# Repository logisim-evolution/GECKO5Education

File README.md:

# GECKO5Education

The Gecko5Education is a new take on an open hardware educational platform. The ideas
of the Gecko5Education are based on the open hardware [ULX3S](https://github.com/emard/ulx3s) board,
the [Gecko4Education](https://gecko-wiki.ti.bfh.ch/) line of boards, and the recently developed 
[Leguan development board](https://leguan.ti.bfh.ch/).

3D preview:

This is a small (60.6x100 mm) standalone FPGA board 
for education, research and general purpose. It's open source and 
open hardware. It continues my line of educational boards used in the
past for teaching and research projects.

# Developer's guide
Information on how to use the board can be found [here](https://gecko5education.ti.bfh.ch)

# Production
The prototypes for these boards were produced and mounted by [Eurocircuits](https://www.eurocircuits.com/).

# Financement
The prototypes for these board (V1.0 and V1.1) were financed by the [computer architecture lab](https://www.epfl.ch/labs/lap/) of [EPFL](https://www.epfl.ch). Version V1.2 and the CPU-addon was financed by the [HuCE-microlab](https://www.bfh.ch/ti/en/research/research-areas/microlab/) of [BFH](https://www.bfh.ch).

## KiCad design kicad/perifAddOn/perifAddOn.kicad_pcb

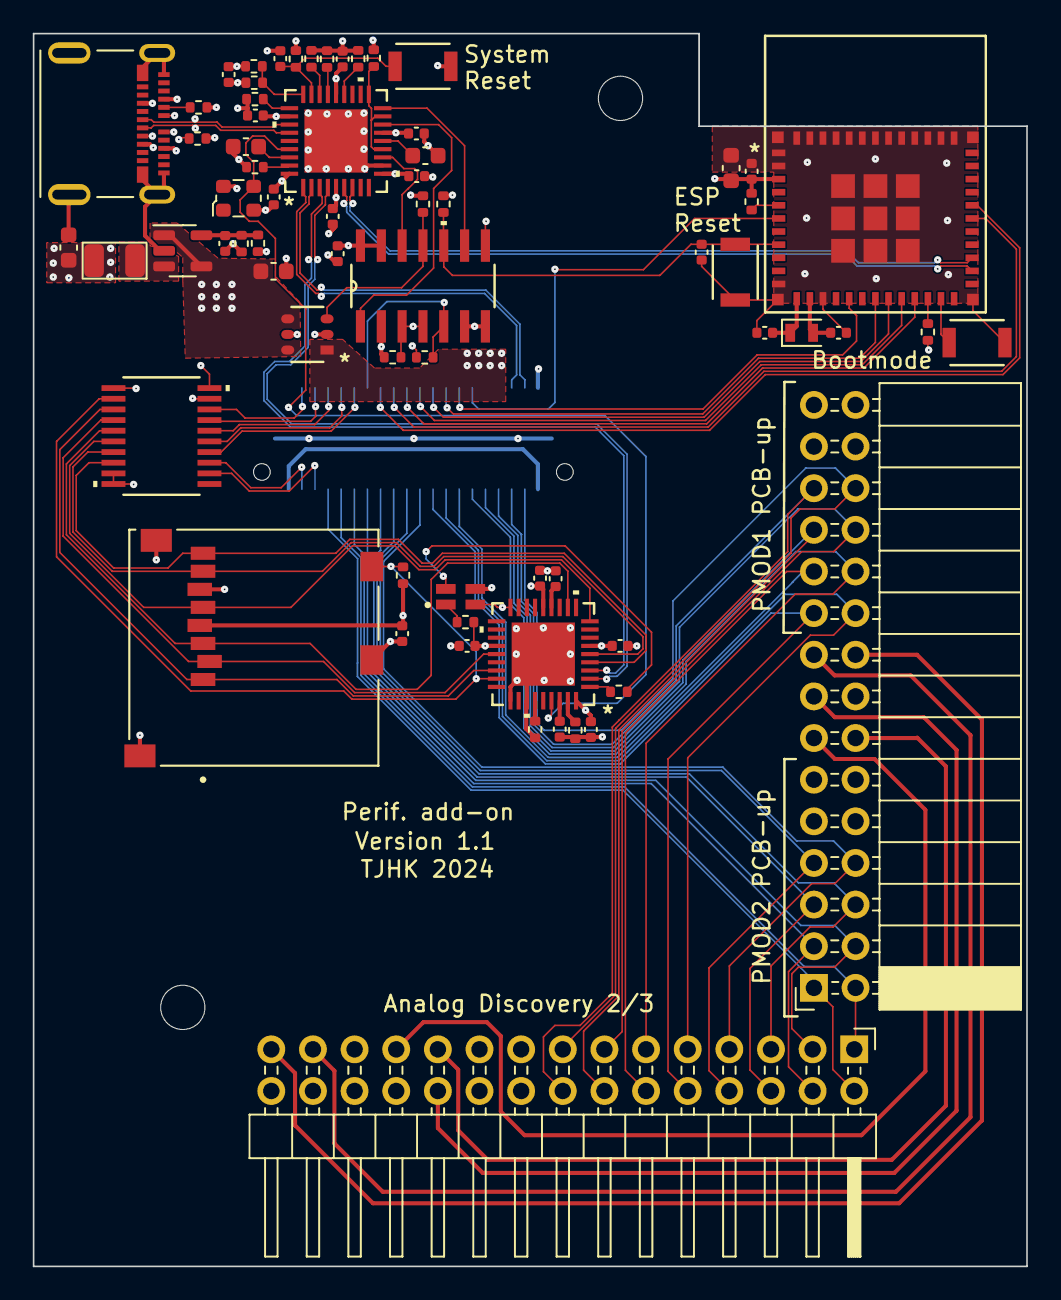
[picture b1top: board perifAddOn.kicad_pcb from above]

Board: 4 copper layers, 60.6 x 75.2 mm, 69 parts (1 on the bottom side), 90 nets.

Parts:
C1, C2, C4, C5, C6, C7, C8, C13, C14, C15, C19, C20, C22, C23, C24, C26: 100n; C_0402_1005Metric
C3, C9, C11, C12, C18: C1608X5R0J106M080AB; C_0603_1608Metric
C10: 18p; C_0402_1005Metric
C16, C17: 9pF; C_0402_1005Metric
C21, C25: 1uF; C_0402_1005Metric
D1: APHBM2012SURKCGKC; LED_APHBM2012SURKCGKC
J1: QTE-020-01-X-D-A; SAMTEC_QTE-020-01-X-D-A
J2: 105450-0101; MOLEX_105450-0101
J3: GTFP08431BEU; AMPHENOL_GTFP08431BEU
J4: Conn_02x15_Odd_Even; PinHeader_2x15_P2.54mm_Horizontal
J5: Conn_02x15_Odd_Even; PinSocket_2x15_P2.54mm_Horizontal
L1: LQM2HPN2R2MJ0L
R1, R2: 5k1; R_0402_1005Metric
R3, R4, R5, R6, R9, R10, R11, R12, R17, R18, R19, R20, R21, R24: 10k; R_0402_1005Metric
R7: 680k; R_0402_1005Metric
R8: 150k; R_0402_1005Metric
R13: 12k; R_0402_1005Metric
R14, R15, R16: 100k; R_0402_1005Metric
R22: 768R; R_0402_1005Metric
R23: 330R; R_0402_1005Metric
SW1, SW2, SW3: B3U-1000P[]; SW_B3U-1000P_OMR
U1: AP2281-3WG-7; SOT26_DIO
U2: SN74HC266DR; D14
U3: USB2513B-AEZC; QFN36_6X6MC_MCH
U4: NCP1529A; SOT-23-5
U5: ESP32-C3-MINI-1-N4; ESP32-C3-MINI-1_EXP
U6: USB2244-AEZG-06; QFN36_6X6MC_MCH
U7: TC7MBL3245CFTEL; TSSOP20_TOS
X1: ECS-2520MV-240-BL-TR; Oscillator_SMD_ECS_2520MV-xxx-xx-4Pin_2.5x2.0mm
Y1: RT2012-32.768-9-20-EXT-TR; Crystal_SMD_2012-2Pin_2.0x1.2mm

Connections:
+3.3V: C1.1, C2.1, C4.1, C5.1, C6.1, C7.1, C8.1, C10.1, C11.1, C15.2, C18.1, C20.2, C22.1, C23.1, C24.1, C26.1, J3.4 (VDD), J5.11, J5.12, J5.29, J5.30, L1.2, R3.2, R4.1, R5.1, R6.2, R7.1, R16.2, R17.2, R18.2, R19.2, R22.1, U2.2 (1B), U2.8 (3A), U2.13 (4B), U2.14 (VCC), U3.5 (VDDA33), U3.10 (VDDA33), U3.15 (VDD33), U3.23 (VDD33), U3.29 (VDDA33), U3.36 (VDD33), U5.3 (3V3), U6.6 (VDD33), U6.14 (VDD33), U6.22 (VDD33), U6.36 (VDDA33), U7.20, X1.4 (VDD)
+5V: C9.1, C13.1, J2.A4 (VBUS1), J2.A9 (VBUS2), J2.B4 (VBUS3), J2.B9 (VBUS4), R14.2, U1.4 (IN), U1.6 (IN), U4.1 (EN), U4.4 (VIN)
ADC_ChanA: J4.21, J5.14
ADC_ChanB: J4.22, J5.15
Clock24MHz: U3.33 (XTALIN/CLKIN), U6.33 (XTAL1(CLKIN)), X1.3 (OUT)
D1+: J2.A6 (D1+), J2.B6 (D2+), U3.31 (USBDP_UP)
D1-: J2.A7 (D1-), J2.B7 (D2-), U3.30 (USBDM_UP)
DAC_ChanA: J4.27, J5.17
DAC_ChanB: J4.29, J5.18
ESP32Drive: U2.9 (3B), U3.18 (PRTPWR3/BC_EN3)
EnFPGA: R4.2, U1.3 (EN), U2.11 (4Y)
EspD+: U3.7 (USBDP_DN3/PRT_DIS_P3), U5.27 (IO19)
EspD-: U3.6 (USBDM_DN3/PRT_DIS_M3), U5.26 (IO18)
EspEnable: C19.1, R5.2, SW2.1, U2.10 (3Y), U5.8 (EN)
EspIO3: J1.30, U5.6 (IO3)
EspIO4: J1.26, U5.18 (IO4)
EspIO5: J1.24, U5.19 (IO5)
EspIO6: J1.22, U5.20 (IO6)
EspIO7: J1.20, U5.21 (IO7)
EspIO10: J1.28, U5.16 (IO10)
EspRxd: J1.18, U5.30 (RXD0)
EspTxd: J1.16, U5.31 (TXD0)
FPGADrive: U2.12 (4A), U3.12 (PRTPWR1/BC_EN1)
GND: C1.2, C2.2, C3.2, C4.2, C5.2, C6.2, C7.2, C8.2, C9.2, C11.2, C12.2, C13.2, C14.2, C15.1, C16.2, C17.2, C18.2, C19.2, C20.1, C21.2, C22.2, C23.2, C24.2, C25.2, C26.2, D1.3, J1.40, J1.G1 (GND), J1.G2 (GND), J1.G3 (GND), J1.G4 (GND), J2.A1 (GND1), J2.A12 (GND2), J2.B1 (GND3), J2.B12 (GND4), J2.S1 (SHIELD), J2.S2 (SHIELD), J2.S3 (SHIELD), J2.S4 (SHIELD), J3.6 (VSS), J3.G1 (SHIELD_GND), J3.G2 (SHIELD_GND__1), J3.G3 (SHIELD_GND__2), J4.19, J4.20, J4.24, J4.25, J4.26, J4.28, J4.30, J5.9, J5.10, J5.16, J5.27, J5.28, R1.1, R2.1, R8.2, R9.1, R10.1, R11.1, R12.1, R13.1, R15.1, R20.2, R21.2, R24.2, SW1.2, SW2.2, SW3.2, U1.2 (GND), U1.5 (GND), U2.6 (2B), U2.7 (GND), U3.11 (TEST), U3.37 (EPAD), U4.2 (GND), U5.1 (GND), U5.2 (GND), U5.11 (GND), U5.14 (GND), U5.36 (GND), U5.37 (GND), U5.38 (GND), U5.39 (GND), U5.40 (GND), U5.41 (GND), U5.42 (GND), U5.43 (GND), U5.44 (GND), U5.45 (GND), U5.46 (GND), U5.47 (GND), U5.48 (GND), U5.49 (GND), U5.50 (GND), U5.51 (GND), U5.52 (GND), U5.53 (GND), U5.54 (GND), U5.55 (GND), U5.56 (GND), U5.57 (GND), U5.58 (GND), U5.59 (GND), U5.60 (GND), U5.61 (GND), U6.28 (TEST), U6.30 (SD_WP), U6.37 (EPAD), U7.1, U7.9, U7.10, X1.2 (GND)
unnamed: D1.1, R22.2
unnamed: D1.4, R23.2
unnamed: J1.01, J1.39
unnamed: J2.A5 (CC1), R1.2
unnamed: J2.B5 (CC2), R2.2
unnamed: J1.32, J1.34, U1.1 (OUT)
unnamed: C3.1, U3.14 (CRFILT)
unnamed: R10.2, U3.25 (HS_IND/CFG_SEL1)
unnamed: R6.1, U3.13 (OCS_N1), U3.17 (OCS_N2), U3.19 (OCS_N3)
unnamed: C12.1, U3.34 (PLLFILT)
unnamed: R13.2, U3.35 (RBIAS)
unnamed: C14.1, R16.1, SW1.1, U3.26 (RESET_N)
unnamed: R11.2, U3.24 (SCL/SMBCLK/CFG_SEL0)
unnamed: R12.2, U3.22 (SDA/SMBDATA/NON_REM1)
unnamed: R9.2, U3.28 (SUSP_IND/LOCAL_PWR/NON_REM0)
unnamed: R14.1, R15.2, U3.27 (VBUS_DET)
unnamed: C10.2, R7.2, R8.1, U4.5 (FB)
unnamed: L1.1, U4.3 (SW)
unnamed: C17.1, U5.12 (IO0), Y1.1
unnamed: C16.1, U5.13 (IO1), Y1.2
unnamed: R17.1, U5.5 (IO2)
unnamed: R18.1, U5.22 (IO8)
unnamed: SW3.1, U5.23 (IO9)
unnamed: R23.1, U6.1 (LED)
unnamed: R21.1, U6.35 (RBIAS)
unnamed: R20.1, U6.31 (TXD/SCK)
unnamed: C25.1, U6.13 (VDD18)
unnamed: C21.1, U6.34 (VDD18PLL)
PMOD1_1: J1.23, J4.10, J5.19
PMOD1_2: J1.27, J4.12, J5.21
PMOD1_3: J1.31, J4.14, J5.23
PMOD1_4: J1.35, J4.16, J5.25
PMOD1_7: J1.25, J4.9, J5.20
PMOD1_8: J1.29, J4.11, J5.22
PMOD1_9: J1.33, J4.13, J5.24
PMOD1_10: J1.37, J4.15, J5.26
PMOD2_1: J1.07, J4.2, J5.1
PMOD2_2: J1.11, J4.4, J5.3
PMOD2_3: J1.15, J4.6, J5.5
PMOD2_4: J1.19, J4.8, J5.7
PMOD2_7: J1.09, J4.1, J5.2
PMOD2_8: J1.13, J4.3, J5.4
PMOD2_9: J1.17, J4.5, J5.6
PMOD2_10: J1.21, J4.7, J5.8
SDCReset: J1.14, R24.1, U2.5 (2A)
SDCnReset: D1.2, R3.1, U2.3 (1Y), U2.4 (2Y), U6.18 (RESET_N), U7.19
SDCnResetDrive: U2.1 (1A), U3.16 (PRTPWR2/BC_EN2)
SdClk: J3.5 (CLK), U6.9 (SD_CLK), U7.6
SdClkB: J1.12, U7.14
SdCmd: J3.3 (CMD), U6.11 (SD_CMD), U7.5
SdCmdB: J1.10, U7.15
SdD0: J3.7 (DAT0), U6.5 (SD_D0), U7.7
SdD0B: J1.03, U7.13
SdD1: J3.8 (DAT1), U6.4 (SD_D1), U7.8
SdD1B: J1.05, U7.12
SdD2: J3.1 (DAT2), U6.25 (SD_D2), U7.3
SdD2B: J1.06, U7.17
SdD3: J3.2 (CD/DAT3), U6.23 (SD_D3), U7.4
SdD3B: J1.08, U7.16
SdcD+: U3.4 (USBDP_DN2/PRT_DIS_P2), U6.2 (USB+)
SdcD-: U3.3 (USBDM_DN2/PRT_DIS_M2), U6.3 (USB-)
SdnDet: J3.CD_PIN, R19.1, U6.26 (SD_NCD), U7.2
SdnDetB: J1.04, U7.18
UsbD+: J1.38, U3.2 (USBDP_DN1/PRT_DIS_P1)
UsbD-: J1.36, U3.1 (USBDM_DN1/PRT_DIS_M1)
VREF: J4.23, J5.13

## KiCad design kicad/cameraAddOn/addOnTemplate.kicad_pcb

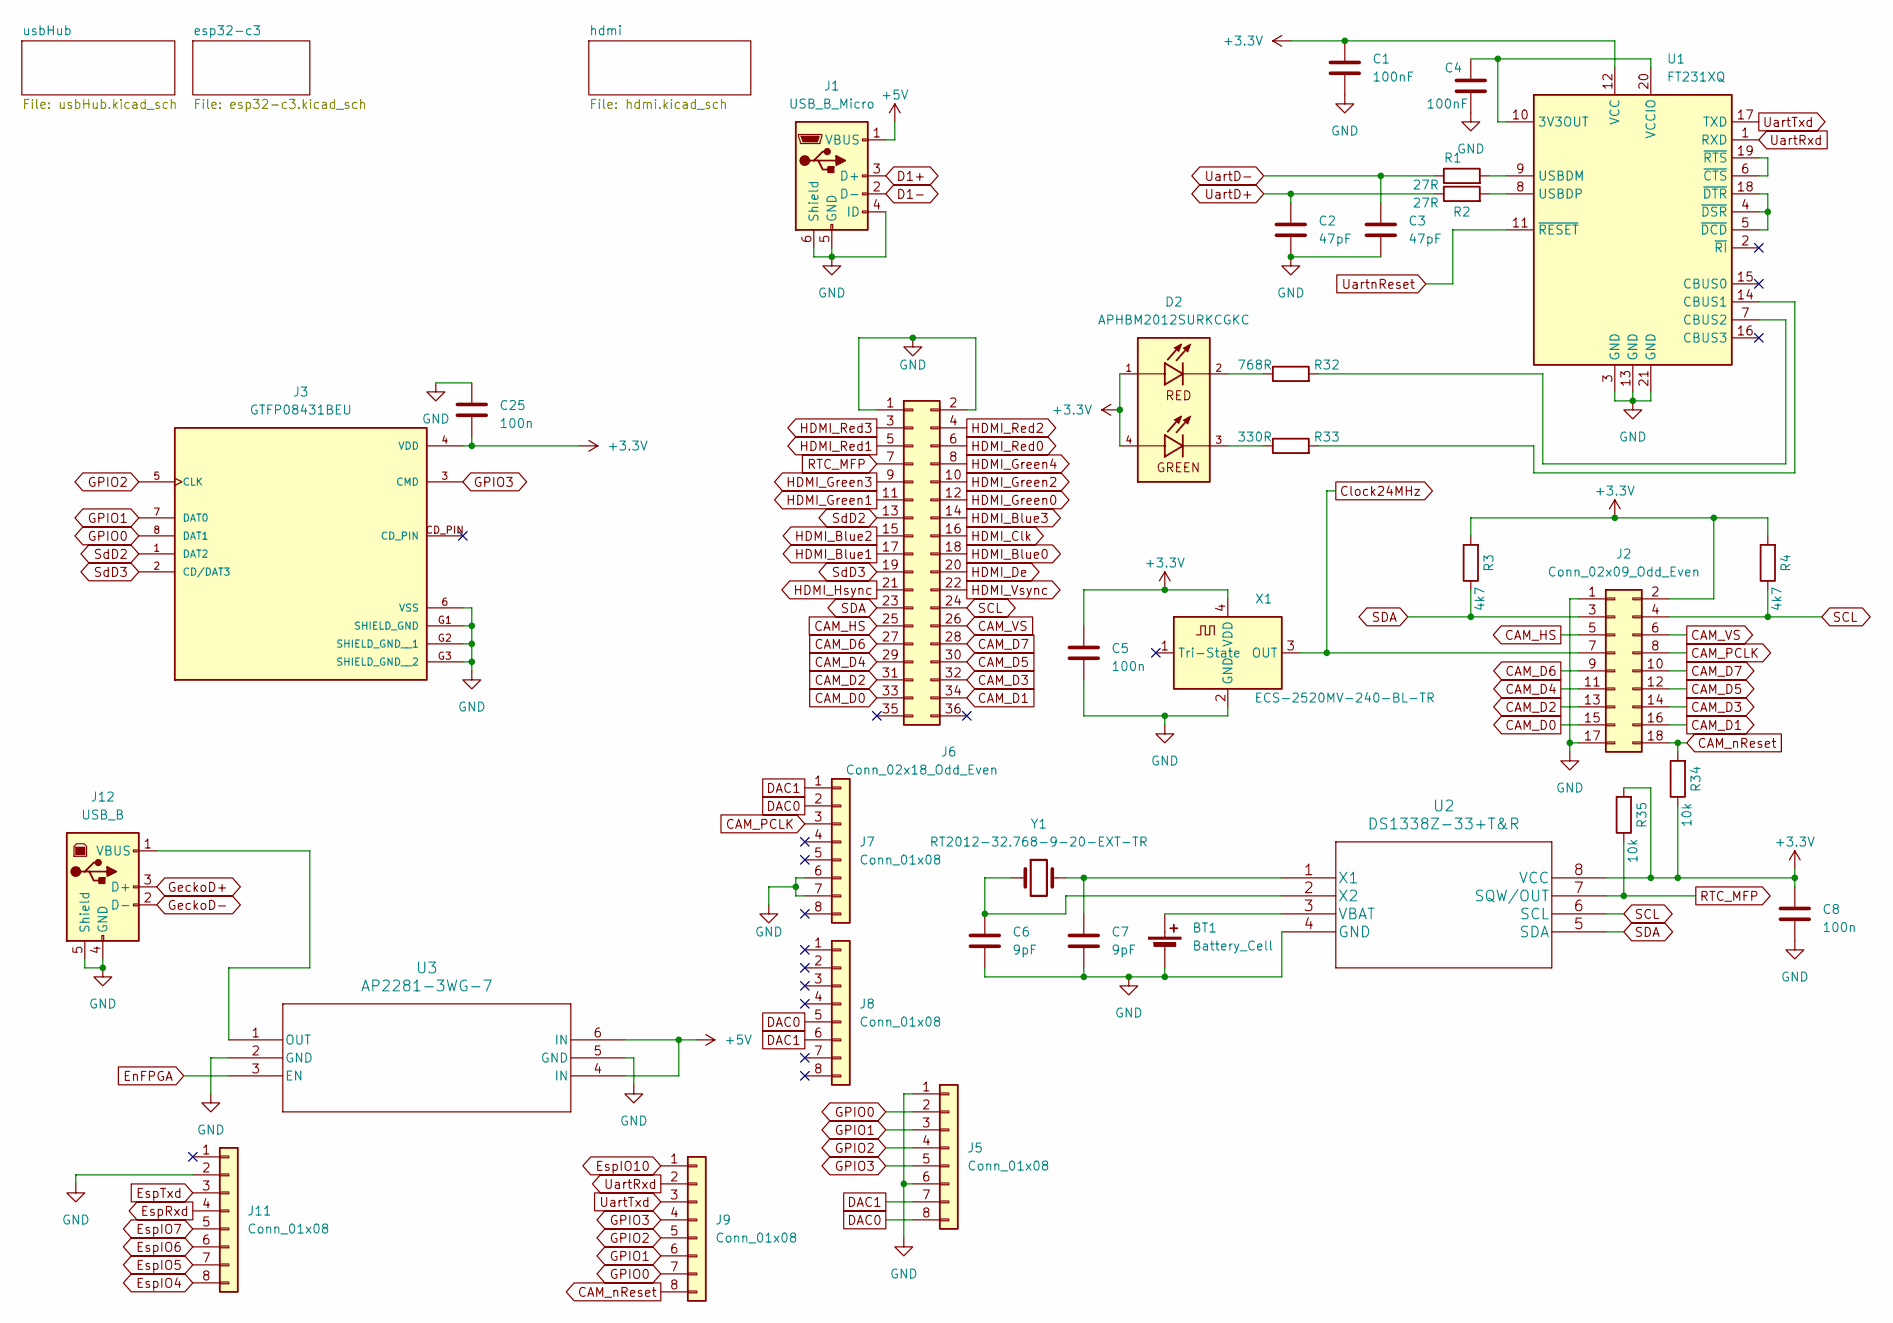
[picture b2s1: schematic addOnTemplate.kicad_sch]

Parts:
BT1: Battery_Cell; BatteryHolder_Keystone_1060_1x2032
C1, C4: 100nF; C_0402_1005Metric
C2, C3: 47pF; C_0402_1005Metric
C5, C8, C25: 100n; C_0402_1005Metric
C6, C7: 9pF; C_0402_1005Metric
D2: APHBM2012SURKCGKC; LED_APHBM2012SURKCGKC
J1: USB_B_Micro; USB_Micro-AB_Molex_47590-0001
J2: Conn_02x09_Odd_Even; PinSocket_2x09_P2.54mm_Horizontal
J3: GTFP08431BEU; AMPHENOL_GTFP08431BEU; PARTREV F
J5: Conn_01x08; PinHeader_2x04_P2.54mm_Horizontal
J6: Conn_02x18_Odd_Even; PinHeader_2x18_P2.54mm_Vertical
J7, J8, J9, J11: Conn_01x08; PinHeader_1x08_P2.54mm_Vertical
J12: USB_B; USB_A_Molex_67643_Horizontal
R1, R2: 27R; R_0402_1005Metric
R3, R4: 4k7; R_0402_1005Metric
R32: 768R; R_0402_1005Metric
R33: 330R; R_0402_1005Metric
R34, R35: 10k; R_0402_1005Metric
U1: FT231XQ; QFN-20-1EP_4x4mm_P0.5mm_EP2.5x2.5mm
U2: DS1338Z-33+T&R; DS1338Z-33&plus_T&R
U3: AP2281-3WG-7; SOT26_DIO
X1: ECS-2520MV-240-BL-TR; Oscillator_SMD_ECS_2520MV-xxx-xx-4Pin_2.5x2.0mm
Y1: RT2012-32.768-9-20-EXT-TR; Crystal_SMD_2012-2Pin_2.0x1.2mm

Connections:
+3.3V: C1.1, C5.1, C8.1, C25.2, D2.1, D2.4, J2.2, J3.4 (VDD), R3.2, R4.2, R34.1, R35.2, U1.12 (VCC), U2.8 (VCC), X1.4 (VDD); also elsewhere on the board
+5V: J1.1 (VBUS), U3.4 (IN), U3.6 (IN); also elsewhere on the board
CAM_D0: J2.15, J6.33
CAM_D1: J2.16, J6.34
CAM_D2: J2.13, J6.31
CAM_D3: J2.14, J6.32
CAM_D4: J2.11, J6.29
CAM_D5: J2.12, J6.30
CAM_D6: J2.9, J6.27
CAM_D7: J2.10, J6.28
CAM_HS: J2.5, J6.25
CAM_PCLK: J2.8, J7.3
CAM_VS: J2.6, J6.26
CAM_nReset: J2.18, J9.8, R34.2
Clock24MHz: J2.7, X1.3 (OUT); also elsewhere on the board
D1+: J1.3 (D+); also elsewhere on the board
D1-: J1.2 (D-); also elsewhere on the board
DAC0: J5.8, J7.2, J8.5
DAC1: J5.7, J7.1, J8.6
EnFPGA: U3.3 (EN); also elsewhere on the board
EspIO4: J11.8; also elsewhere on the board
EspIO5: J11.7; also elsewhere on the board
EspIO6: J11.6; also elsewhere on the board
EspIO7: J11.5; also elsewhere on the board
EspIO10: J9.1; also elsewhere on the board
EspRxd: J11.4; also elsewhere on the board
EspTxd: J11.3; also elsewhere on the board
GND: BT1.2 (-), C1.2, C2.2, C3.2, C4.2, C5.2, C6.2, C7.2, C8.2, C25.1, J1.4 (ID), J1.5 (GND), J1.6 (Shield), J2.1, J2.17, J3.6 (VSS), J3.G1 (SHIELD_GND), J3.G2 (SHIELD_GND__1), J3.G3 (SHIELD_GND__2), J5.1, J5.6, J6.1, J6.2, J7.6, J7.7, J11.2, J12.4 (GND), J12.5 (Shield), U1.3 (GND), U1.13 (GND), U1.21 (GND), U2.4 (GND), U3.2 (GND), U3.5 (GND), X1.2 (GND); also elsewhere on the board
GPIO0: J3.8 (DAT1), J5.2, J9.7
GPIO1: J3.7 (DAT0), J5.3, J9.6
GPIO2: J3.5 (CLK), J5.4, J9.5
GPIO3: J3.3 (CMD), J5.5, J9.4
GeckoD+: J12.3 (D+); also elsewhere on the board
GeckoD-: J12.2 (D-); also elsewhere on the board
HDMI_Blue0: J6.18; also elsewhere on the board
HDMI_Blue1: J6.17; also elsewhere on the board
HDMI_Blue2: J6.15; also elsewhere on the board
HDMI_Blue3: J6.14; also elsewhere on the board
HDMI_Clk: J6.16; also elsewhere on the board
HDMI_De: J6.20; also elsewhere on the board
HDMI_Green0: J6.12; also elsewhere on the board
HDMI_Green1: J6.11; also elsewhere on the board
HDMI_Green2: J6.10; also elsewhere on the board
HDMI_Green3: J6.9; also elsewhere on the board
HDMI_Green4: J6.8; also elsewhere on the board
HDMI_Hsync: J6.21; also elsewhere on the board
HDMI_Red0: J6.6; also elsewhere on the board
HDMI_Red1: J6.5; also elsewhere on the board
HDMI_Red2: J6.4; also elsewhere on the board
HDMI_Red3: J6.3; also elsewhere on the board
HDMI_Vsync: J6.22; also elsewhere on the board
unnamed: BT1.1 (+), U2.3 (VBAT)
unnamed: D2.2, R32.1
unnamed: D2.3, R33.1
unnamed: J12.1 (VBUS), U3.1 (OUT)
unnamed: C4.1, U1.10 (3V3OUT), U1.20 (VCCIO)
unnamed: R33.2, U1.14 (CBUS1)
unnamed: R32.2, U1.7 (CBUS2)
unnamed: R1.2, U1.9 (USBDM)
unnamed: R2.2, U1.8 (USBDP)
unnamed: U1.6 (~CTS), U1.19 (~RTS)
unnamed: U1.4 (~DSR), U1.5 (~DCD), U1.18 (~DTR)
unnamed: C7.1, U2.1 (X1), Y1.2
unnamed: C6.1, U2.2 (X2), Y1.1
RTC_MFP: J6.7, R35.1, U2.7 (SQW/OUT)
SCL: J2.4, J6.24, R4.1, U2.6 (SCL)
SDA: J2.3, J6.23, R3.1, U2.5 (SDA)
SdD2: J3.1 (DAT2), J6.13
SdD3: J3.2 (CD/DAT3), J6.19
UartD+: C2.1, R2.1; also elsewhere on the board
UartD-: C3.1, R1.1; also elsewhere on the board
UartRxd: J9.2, U1.1 (RXD)
UartTxd: J9.3, U1.17 (TXD)
UartnReset: U1.11 (~RESET); also elsewhere on the board

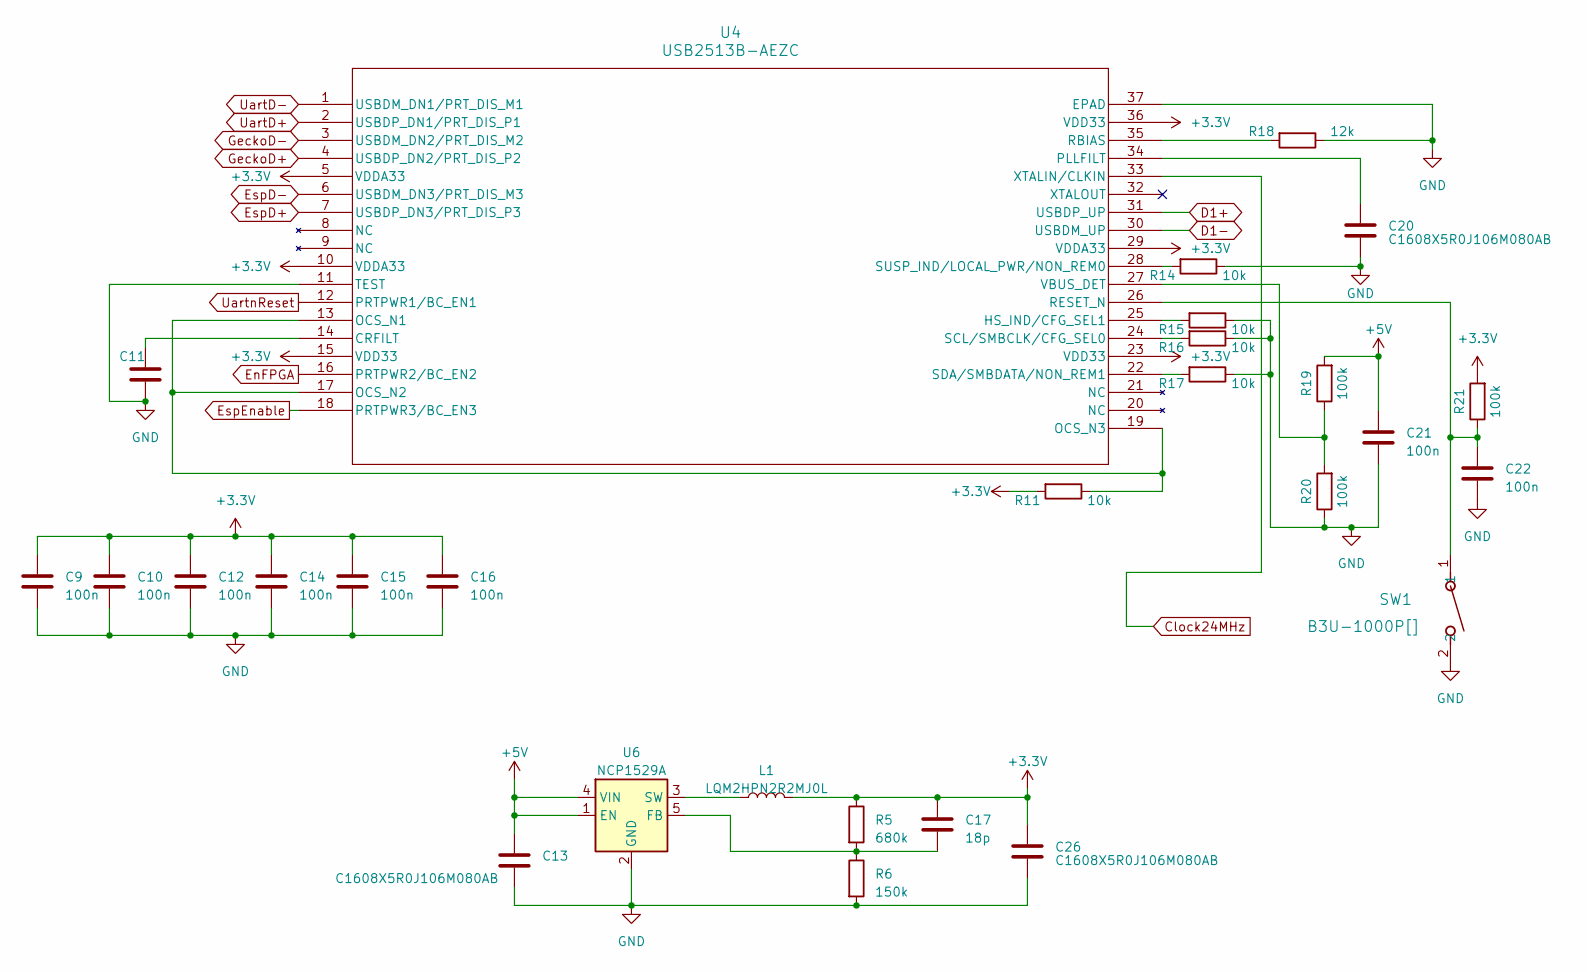
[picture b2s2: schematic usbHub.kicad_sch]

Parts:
C9, C10, C12, C14, C15, C16, C21, C22: 100n; C_0402_1005Metric
C11, C13, C20, C26: C1608X5R0J106M080AB; C_0603_1608Metric
C17: 18p; C_0402_1005Metric
L1: LQM2HPN2R2MJ0L
R5: 680k; R_0402_1005Metric
R6: 150k; R_0402_1005Metric
R11, R14, R15, R16, R17: 10k; R_0402_1005Metric
R18: 12k; R_0402_1005Metric
R19, R20, R21: 100k; R_0402_1005Metric
SW1: B3U-1000P[]; SW_B3U-1000P_OMR
U4: USB2513B-AEZC; QFN36_6X6MC_MCH
U6: NCP1529A; SOT-23-5

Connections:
+3.3V: C9.1, C10.1, C12.1, C14.1, C15.1, C16.1, C17.1, C26.1, L1.2, R5.1, R11.2, R21.2, U4.5 (VDDA33), U4.10 (VDDA33), U4.15 (VDD33), U4.23 (VDD33), U4.29 (VDDA33), U4.36 (VDD33); also elsewhere on the board
+5V: C13.1, C21.1, R19.2, U6.1 (EN), U6.4 (VIN); also elsewhere on the board
Clock24MHz: U4.33 (XTALIN/CLKIN); also elsewhere on the board
D1+: U4.31 (USBDP_UP); also elsewhere on the board
D1-: U4.30 (USBDM_UP); also elsewhere on the board
EnFPGA: U4.16 (PRTPWR2/BC_EN2); also elsewhere on the board
EspD+: U4.7 (USBDP_DN3/PRT_DIS_P3); also elsewhere on the board
EspD-: U4.6 (USBDM_DN3/PRT_DIS_M3); also elsewhere on the board
EspEnable: U4.18 (PRTPWR3/BC_EN3); also elsewhere on the board
GND: C9.2, C10.2, C11.2, C12.2, C13.2, C14.2, C15.2, C16.2, C20.2, C21.2, C22.2, C26.2, R6.2, R14.1, R15.1, R16.1, R17.1, R18.1, R20.1, SW1.2, U4.11 (TEST), U4.37 (EPAD), U6.2 (GND); also elsewhere on the board
GeckoD+: U4.4 (USBDP_DN2/PRT_DIS_P2); also elsewhere on the board
GeckoD-: U4.3 (USBDM_DN2/PRT_DIS_M2); also elsewhere on the board
unnamed: C11.1, U4.14 (CRFILT)
unnamed: R15.2, U4.25 (HS_IND/CFG_SEL1)
unnamed: R11.1, U4.13 (OCS_N1), U4.17 (OCS_N2), U4.19 (OCS_N3)
unnamed: C20.1, U4.34 (PLLFILT)
unnamed: R18.2, U4.35 (RBIAS)
unnamed: C22.1, R21.1, SW1.1, U4.26 (RESET_N)
unnamed: R16.2, U4.24 (SCL/SMBCLK/CFG_SEL0)
unnamed: R17.2, U4.22 (SDA/SMBDATA/NON_REM1)
unnamed: R14.2, U4.28 (SUSP_IND/LOCAL_PWR/NON_REM0)
unnamed: R19.1, R20.2, U4.27 (VBUS_DET)
unnamed: C17.2, R5.2, R6.1, U6.5 (FB)
unnamed: L1.1, U6.3 (SW)
UartD+: U4.2 (USBDP_DN1/PRT_DIS_P1); also elsewhere on the board
UartD-: U4.1 (USBDM_DN1/PRT_DIS_M1); also elsewhere on the board
UartnReset: U4.12 (PRTPWR1/BC_EN1); also elsewhere on the board

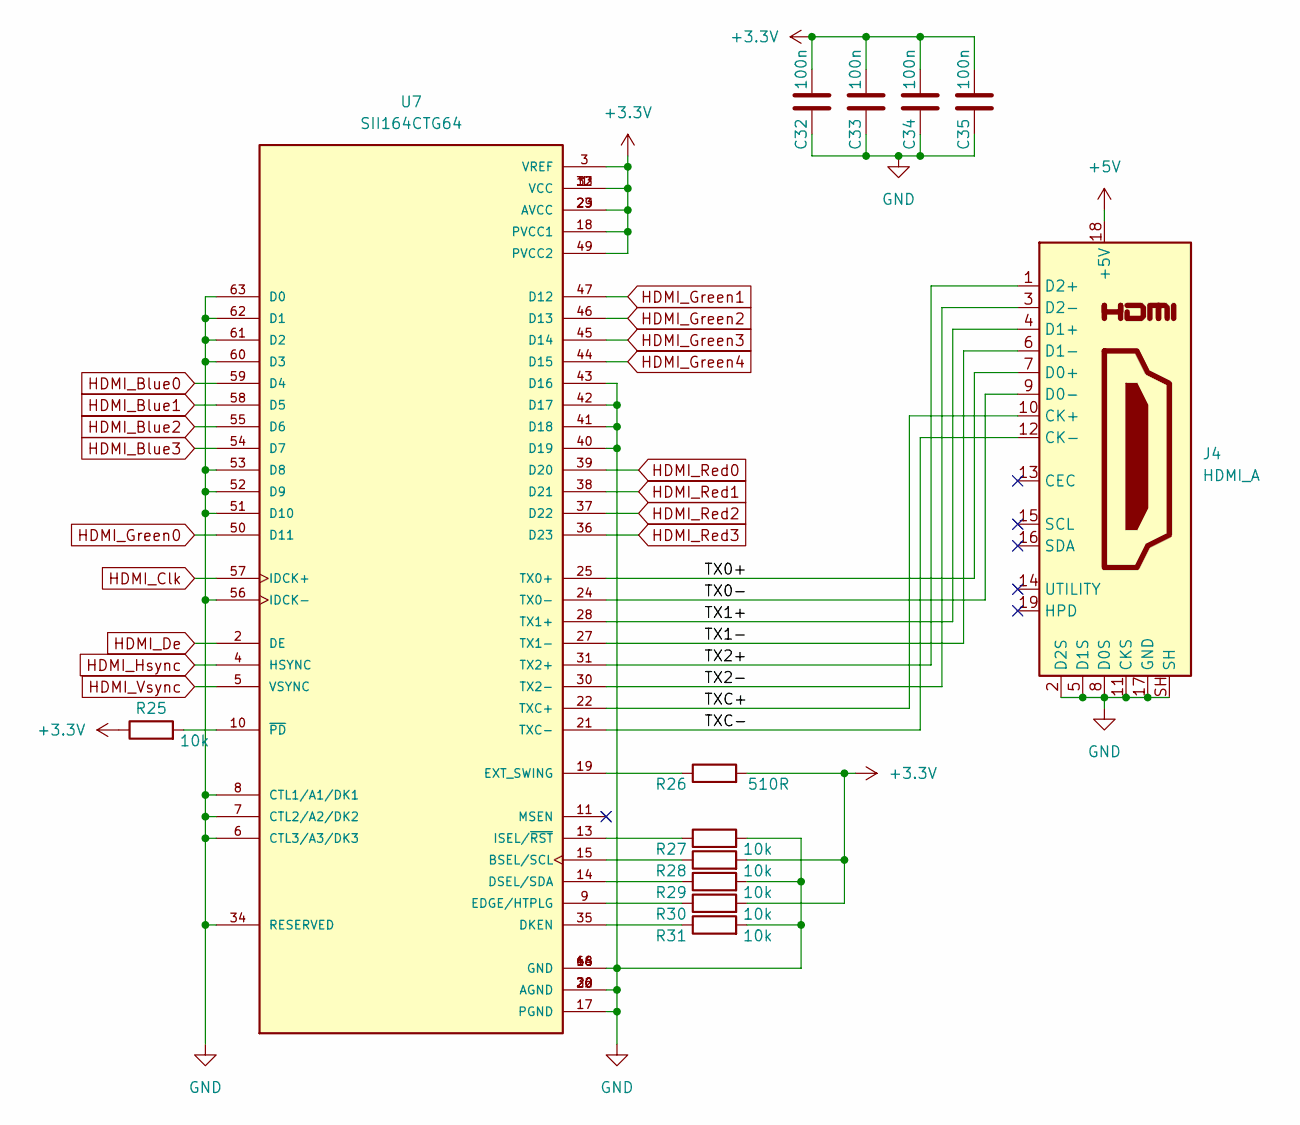
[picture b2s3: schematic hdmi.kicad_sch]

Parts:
C32, C33, C34, C35: 100n; R_0402_1005Metric
J4: HDMI_A; HDMI_A_Molex_208658-1001_Horizontal
R25, R27, R28, R29, R30, R31: 10k; R_0402_1005Metric
R26: 510R; R_0402_1005Metric
U7: SII164CTG64; QFP50P1200X1200X120-64N; PARTREV E; DigiKey_Part_Number 220-2189-ND

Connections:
+3.3V: C32.2, C33.2, C34.2, C35.2, R25.1, R26.2, R28.2, R30.2, U7.1 (VCC), U7.3 (VREF), U7.12 (VCC), U7.18 (PVCC1), U7.23 (AVCC), U7.29 (AVCC), U7.33 (VCC), U7.49 (PVCC2); also elsewhere on the board
+5V: J4.18 (+5V); also elsewhere on the board
/hdmi/TX0+: J4.7 (D0+), U7.25 (TX0+)
/hdmi/TX0-: J4.9 (D0-), U7.24 (TX0-)
/hdmi/TX1+: J4.4 (D1+), U7.28 (TX1+)
/hdmi/TX1-: J4.6 (D1-), U7.27 (TX1-)
/hdmi/TX2+: J4.1 (D2+), U7.31 (TX2+)
/hdmi/TX2-: J4.3 (D2-), U7.30 (TX2-)
/hdmi/TXC+: J4.10 (CK+), U7.22 (TXC+)
/hdmi/TXC-: J4.12 (CK-), U7.21 (TXC-)
GND: C32.1, C33.1, C34.1, C35.1, J4.2 (D2S), J4.5 (D1S), J4.8 (D0S), J4.11 (CKS), J4.17 (GND), J4.SH, R27.2, R29.2, R31.2, U7.6 (CTL3/A3/DK3), U7.7 (CTL2/A2/DK2), U7.8 (CTL1/A1/DK1), U7.16 (GND), U7.17 (PGND), U7.20 (AGND), U7.26 (AGND), U7.32 (AGND), U7.34 (RESERVED), U7.40 (D19), U7.41 (D18), U7.42 (D17), U7.43 (D16), U7.48 (GND), U7.51 (D10), U7.52 (D9), U7.53 (D8), U7.56 (IDCK-), U7.60 (D3), U7.61 (D2), U7.62 (D1), U7.63 (D0), U7.64 (GND); also elsewhere on the board
HDMI_Blue0: U7.59 (D4); also elsewhere on the board
HDMI_Blue1: U7.58 (D5); also elsewhere on the board
HDMI_Blue2: U7.55 (D6); also elsewhere on the board
HDMI_Blue3: U7.54 (D7); also elsewhere on the board
HDMI_Clk: U7.57 (IDCK+); also elsewhere on the board
HDMI_De: U7.2 (DE); also elsewhere on the board
HDMI_Green0: U7.50 (D11); also elsewhere on the board
HDMI_Green1: U7.47 (D12); also elsewhere on the board
HDMI_Green2: U7.46 (D13); also elsewhere on the board
HDMI_Green3: U7.45 (D14); also elsewhere on the board
HDMI_Green4: U7.44 (D15); also elsewhere on the board
HDMI_Hsync: U7.4 (HSYNC); also elsewhere on the board
HDMI_Red0: U7.39 (D20); also elsewhere on the board
HDMI_Red1: U7.38 (D21); also elsewhere on the board
HDMI_Red2: U7.37 (D22); also elsewhere on the board
HDMI_Red3: U7.36 (D23); also elsewhere on the board
HDMI_Vsync: U7.5 (VSYNC); also elsewhere on the board
unnamed: R28.1, U7.15 (BSEL/SCL)
unnamed: R31.1, U7.35 (DKEN)
unnamed: R29.1, U7.14 (DSEL/SDA)
unnamed: R30.1, U7.9 (EDGE/HTPLG)
unnamed: R26.1, U7.19 (EXT_SWING)
unnamed: R27.1, U7.13 (ISEL/~RST)
unnamed: R25.2, U7.10 (~PD)

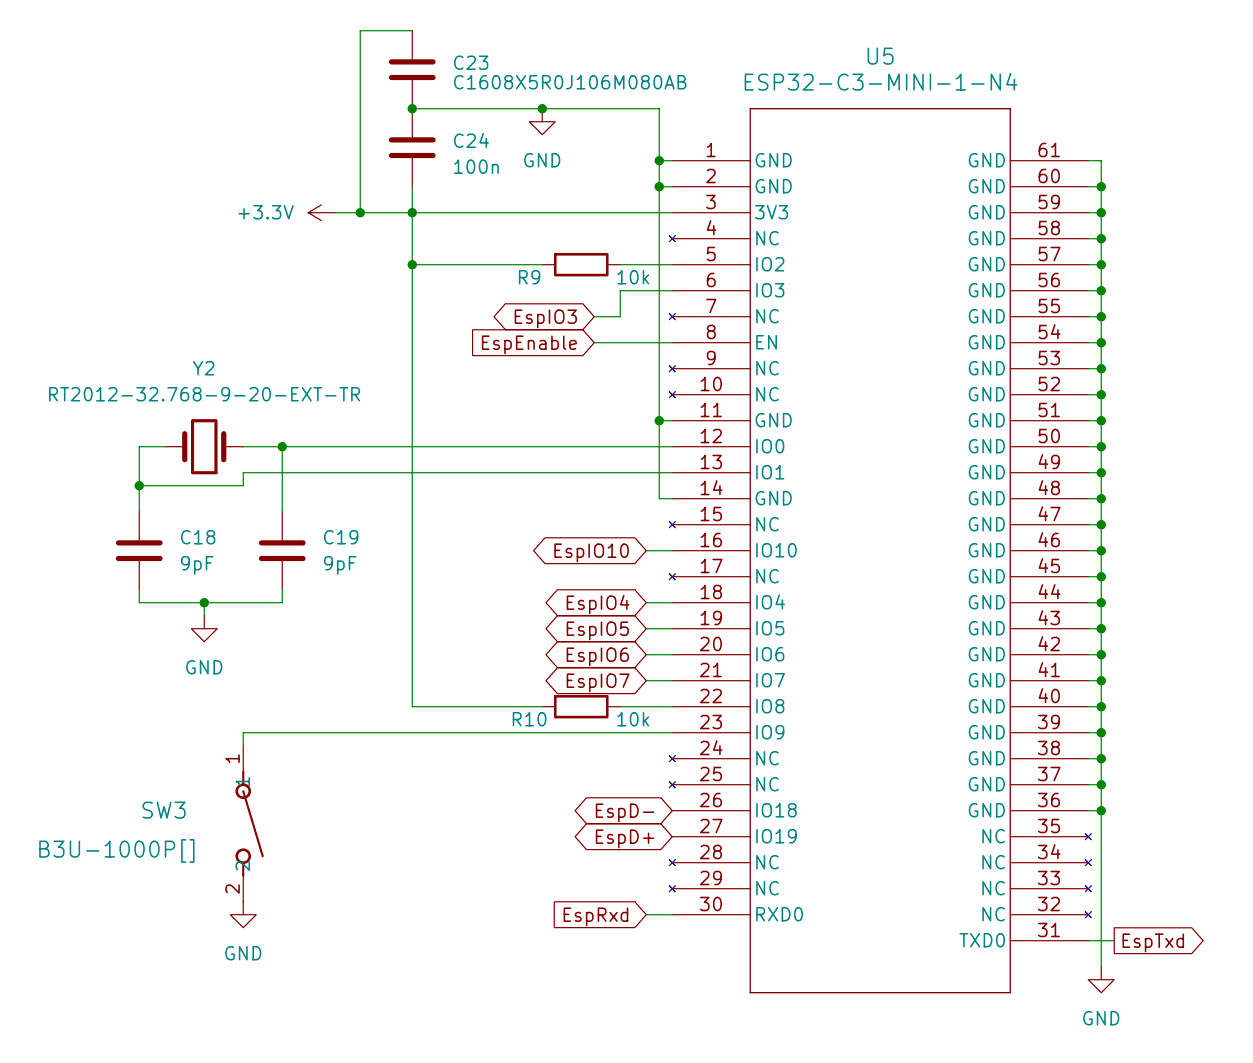
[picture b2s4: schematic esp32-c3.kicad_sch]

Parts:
C18, C19: 9pF; C_0402_1005Metric
C23: C1608X5R0J106M080AB; C_0603_1608Metric
C24: 100n; C_0402_1005Metric
R9, R10: 10k; R_0402_1005Metric
SW3: B3U-1000P[]; SW_B3U-1000P_OMR
U5: ESP32-C3-MINI-1-N4; ESP32-C3-MINI-1_EXP
Y2: RT2012-32.768-9-20-EXT-TR; Crystal_SMD_2012-2Pin_2.0x1.2mm

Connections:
+3.3V: C23.1, C24.2, R9.2, R10.2, U5.3 (3V3); also elsewhere on the board
EspD+: U5.27 (IO19); also elsewhere on the board
EspD-: U5.26 (IO18); also elsewhere on the board
EspEnable: U5.8 (EN); also elsewhere on the board
EspIO3: U5.6 (IO3)
EspIO4: U5.18 (IO4); also elsewhere on the board
EspIO5: U5.19 (IO5); also elsewhere on the board
EspIO6: U5.20 (IO6); also elsewhere on the board
EspIO7: U5.21 (IO7); also elsewhere on the board
EspIO10: U5.16 (IO10); also elsewhere on the board
EspRxd: U5.30 (RXD0); also elsewhere on the board
EspTxd: U5.31 (TXD0); also elsewhere on the board
GND: C18.2, C19.2, C23.2, C24.1, SW3.2, U5.1 (GND), U5.2 (GND), U5.11 (GND), U5.14 (GND), U5.36 (GND), U5.37 (GND), U5.38 (GND), U5.39 (GND), U5.40 (GND), U5.41 (GND), U5.42 (GND), U5.43 (GND), U5.44 (GND), U5.45 (GND), U5.46 (GND), U5.47 (GND), U5.48 (GND), U5.49 (GND), U5.50 (GND), U5.51 (GND), U5.52 (GND), U5.53 (GND), U5.54 (GND), U5.55 (GND), U5.56 (GND), U5.57 (GND), U5.58 (GND), U5.59 (GND), U5.60 (GND), U5.61 (GND); also elsewhere on the board
unnamed: C19.1, U5.12 (IO0), Y2.1
unnamed: C18.1, U5.13 (IO1), Y2.2
unnamed: R9.1, U5.5 (IO2)
unnamed: R10.1, U5.22 (IO8)
unnamed: SW3.1, U5.23 (IO9)

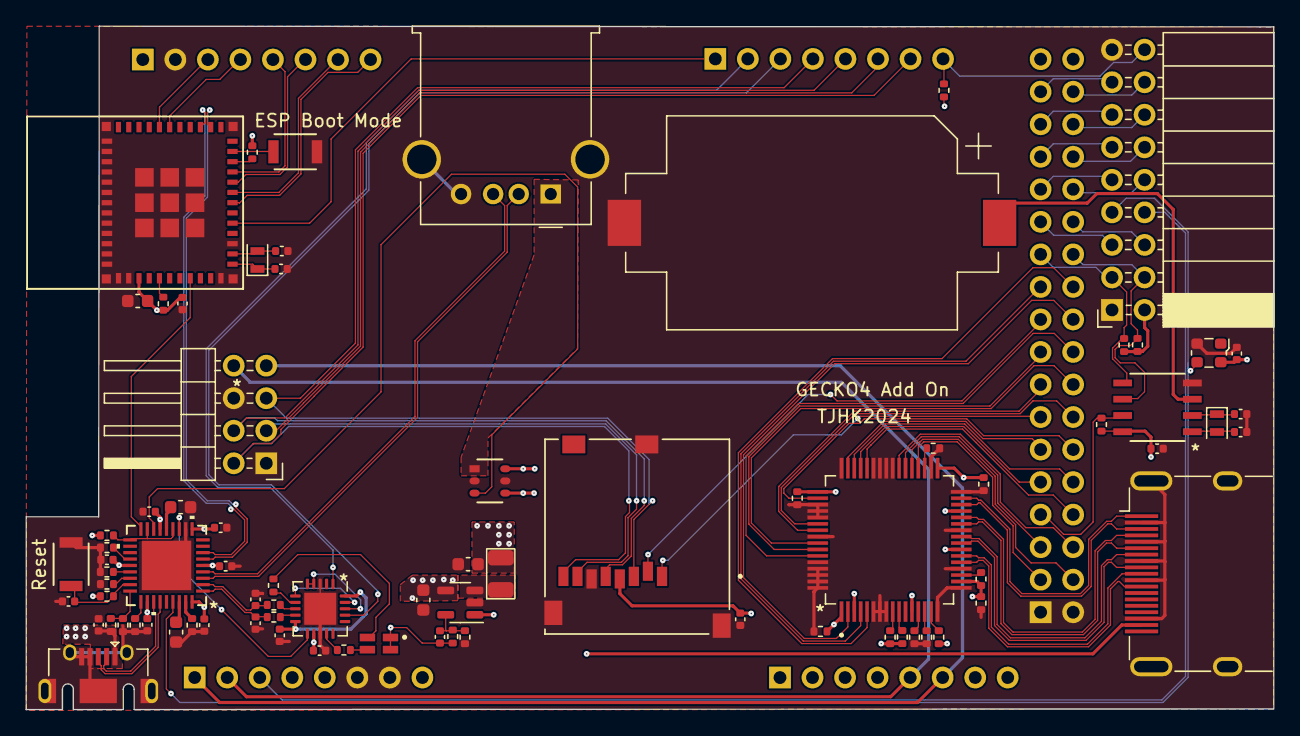
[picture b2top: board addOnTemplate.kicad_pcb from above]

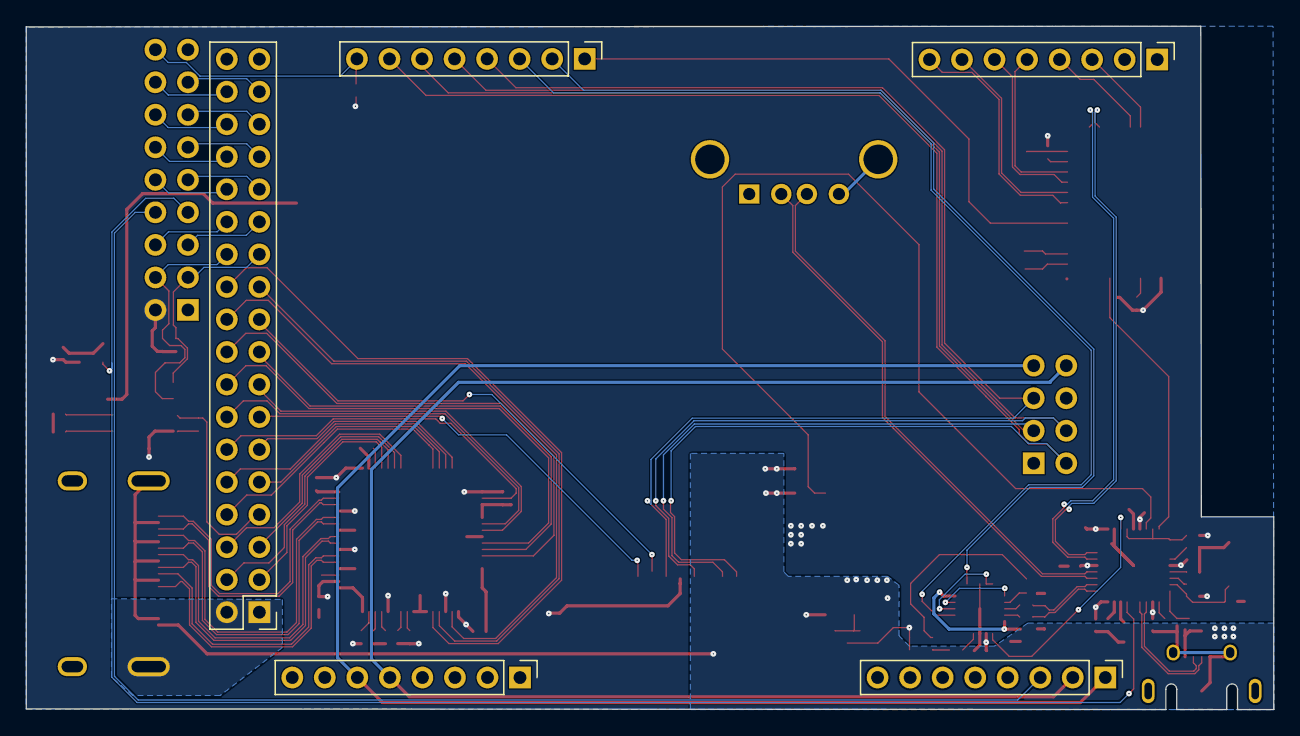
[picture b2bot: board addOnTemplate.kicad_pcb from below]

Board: 2 copper layers, 97.4 x 53.3 mm, 84 parts (5 on the bottom side), 109 nets.

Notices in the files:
parts and their libraries:
Copyright 2016 Accelerated Designs. All rights reserved.
